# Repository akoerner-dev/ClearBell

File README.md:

# ClearBell — Smart-Doorbell (ESP32-S3, Hardware + Firmware)

🇬🇧 [English version](README.en.md)

Selbst entwickeltes Türklingelsystem für ein Zweifamilienhaus — vollständig
eigenentwickelt von der Schaltung über das PCB-Layout bis zur Firmware.
Das Projekt dokumentiert nicht nur *was* gebaut wurde, sondern die
**begründeten Technikentscheidungen** dahinter.

> Leitsatz des Projekts: **„Keep it simple, but working."**

**Aktuelle Generation: V0.2** — Redesign auf den ESP32-S3. Beide Platinen sind fertig
verlegt, bei PCBWay gefertigt und bestückt und in Betrieb genommen. Die erste Generation läuft
im Haus und liegt im [Archiv](archiv/V0.1/).

| Außeneinheit V0.2 | Inneneinheit V0.2 |
|---|---|
|  |  |
| 110 × 60 mm, 4 Lagen, 12 V DC | 98 × 60 mm, 4 Lagen, USB-C |

---

## Überblick

Eine **Außeneinheit** an der Haustür und zwei baugleiche **Inneneinheiten**
(je eine pro Wohnung). Klingeln und Türöffnen laufen als quittierte,
gegen Replay abgesicherte Transaktionen über WLAN/UDP.

| Merkmal | V0.2 |
|---|---|
| Controller | ESP32-S3-WROOM-1-N16R8 (16 MB Flash, 8 MB PSRAM), beide Einheiten |
| Stromversorgung außen | 12 V DC (SELV) → 3,3 V mit LMR33630; Polyfuse, TVS-Diode, Verpolschutz |
| Stromversorgung innen | USB-C 5 V → 3,3 V mit TLV62568 |
| Programmierung | natives USB (USB-Serial-JTAG) — innen über die USB-C-Buchse, außen über eine zusätzliche Service-USB-C |
| Bedienung | kapazitive Touch-Taster mit Bronze-Elektroden, ESD-geschützt |
| Audio | MAX98357A I2S-Class-D, Visaton K 50 FL (außen) / K 50 SQ (innen) |
| Mikrofon | Infineon IM72D128V01 (PDM, IP57) auf beiden Einheiten |
| Anzeige | zweifarbige Status-LED (grün / rot, zusammen bernstein) |
| Türöffner | Low-Side-MOSFET mit Freilaufdiode |
| Kommunikation | WLAN + UDP über den Heim-Router, Türbefehl per HMAC-SHA256 authentifiziert |

---

## Was sich gegenüber V0.1 geändert hat — und warum

- **ESP32-S3 statt ESP32.** Natives USB: Flashen und Logs ohne UART-Adapter und ohne
  Tastendruck. PSRAM für Audiopuffer, Flash-Reserve für zwei OTA-Partitionen, vom
  Hersteller zugesagte Verfügbarkeit bis 2033.
- **Mikrofon auf beiden Einheiten** — als Vorbereitung für späteres Wechselsprechen.
  Die Wahl fiel auf ein PDM-Mikrofon, das direkt an 3,3 V läuft: kein zweiter
  Spannungsbereich, keine Pegelwandler.
- **Keine SD-Karte mehr.** Die Klingeltöne sollen im Flash liegen und über die
  Statusseite getauscht werden — ein Steckverbinder und ein mechanischer Fehlerpfad weniger.
- **4 Lagen statt 2.** Beide Innenlagen sind Masse; jede Signallage hat ihre Bezugsfläche direkt
  darunter. Grund: Bei 1,6 mm liegt der dicke Kern zwangsläufig zwischen den Innenlagen, eine
  eigene Versorgungslage brächte dort kaum Flächenkapazität. Bekannte Abweichung (Inneneinheit):
  Eine 3,3-V-Leitung verläuft auf In2 und unterbricht dort die Massefläche.
  USB D+/D−, I2S_BCLK, I2S_WS und LED_RED auf der Unterseite kreuzen diesen Schlitz; ihr Rückstrom
  muss ausweichen. Funktional unkritisch bei USB Full Speed, aus EMV-Sicht aber vermeidbar.
  Behebung in V0.3: Leitung auf eine Außenlage verlegen, In2 wieder geschlossen.
- **Vias neben den Pads, nicht darin.** Ein Via im Pad zieht beim Reflow Lot ab. Der DRC
  prüft das nicht — deshalb eigene Prüfskripte über alle Vias und Pads.
- **Touch ohne Shield/Guard.** Die Bronze-Elektroden bleiben frei zugänglich. Gegen Drift
  durch Feuchte ist eine adaptive Baseline in der Firmware vorgesehen; die ESD-Dioden haben
  nur 0,5 pF, damit die Empfindlichkeit erhalten bleibt.
- **Türöffner-Freilaufdiode auf 1 A ausgelegt** (SMA-Gehäuse). In V0.1 saß dort eine
  Signaldiode, die für den Spulenstrom des Türöffners zu klein war.

Der Funk-Transport bleibt WLAN/UDP über den Router — ESP-NOW wurde an den echten
Montageorten gemessen und verworfen, siehe
[`docs/Funkvalidierung_ESPNOW.md`](docs/Funkvalidierung_ESPNOW.md).

---

## Repo-Struktur

```
clearbell/
├── hardware/                  V0.2, KiCad 10
│   ├── Ausseneinheit/         Schaltplan, Platine, Schaltplan.pdf
│   │   └── fertigung/         Gerber-ZIP, Stückliste, Bestückungsdaten
│   └── Inneneinheit/          dito
├── firmware/                  V0.2-Firmware (ESP-IDF), Werkzeuge, Testprotokoll
├── docs/
│   ├── img/                   3D-Ansichten V0.2
│   ├── pcbway-review/         Bewertung der PCBWay-Platinen mit Fotos (DE/EN)
│   ├── Softwarearchitektur_V0.2.md      Firmware-Architektur, Laufzeit, Sicherheit
│   ├── Softwarearchitektur_V0.2.en.md   dasselbe auf Englisch
│   └── Funkvalidierung_ESPNOW.md
└── archiv/V0.1/               erste Generation: Hardware, Firmware, Dashboard, Dokumentation
```

---

## Fertigung

| | |
|---|---|
| Lagenaufbau | 4 Lagen, 1,6 mm, FR-4 (S1000H, TG150), 1 oz außen und innen, keine Impedanzkontrolle |
| Oberfläche | HAL bleifrei, Lötstopplack grün, Bestückungsdruck weiß (nur oben) |
| Bestückung | einseitig, maschinell — außen 56, innen 33 Bauteile |
| Stückliste | je Einheit in `fertigung/`, mit Spalte „Ersatz zulässig" (kritische Teile ohne Ersatz) |
| Prüfung | DRC und ERC ohne Befund |

### Erfahrung mit PCBWay

Leiterplatten und Bestückung der V0.2 hat **[PCBWay](https://www.pcbway.com)** übernommen. Die Leiterplatten
wurden im Rahmen eines Sponsorings gefertigt, Bestückung und Bauteile habe ich selbst bezahlt.

Mein Fazit als Leiterplattenentwickler, der beruflich fast täglich Platinen in der Hand hat:

- **Leiterplatten sehr gut:** Lötstopp und Bestückungsdruck sauber und passgenau, HAL-Oberfläche gleichmäßig, keine Delamination,
  Platinen plan und gratfrei.
- **Bestückung sehr gut:** alle Bauteile lagerichtig, kritische Stellen (USB-C, QFN-Audioverstärker, ESP32-S3-Modul)
  ohne Brücken verlötet.
- **Auf Anhieb funktionsfähig:** Inbetriebnahme und 24-Stunden-Dauertest ohne einen einzigen Fertigungsfehler.
- **Kommunikation sehr gut:** fachlich sinnvolle Rückfragen zur Stückliste, Auftragsfortschritt auf der Website
  Schritt für Schritt nachvollziehbar.

Ich würde PCBWay wieder beauftragen.

📋 [**Ausführliche Bewertung mit Fotos**](docs/pcbway-review/README.md) · 🇬🇧 [English version](docs/pcbway-review/README.en.md)

---

## Firmware

Die **V0.2-Firmware** liegt unter [`firmware/`](firmware/README.md): ein ESP-IDF-Projekt (v5.5.5) mit dem
Arduino-Core als Komponente, ein Image für außen und eins für innen. Sie ist portiert, auf allen drei Boards
getestet und am 12.11.2026 abgenommen. Enthalten sind unter anderem ein authentifiziertes Protokoll mit Sitzungen,
Türbefehl per Challenge–Response, Touch mit adaptiver Baseline, Statusseite mit Gerätepasswort, Fern-Öffnen per
Push aufs Handy, Einrichtung ohne PC über ein eigenes WLAN und signierte Updates mit Rückfall. Den Stand jedes
Schritts und die Belege zeigen das [Firmware-README](firmware/README.md) und das
[Testprotokoll](firmware/docs/Testprotokoll.md). Offen sind noch der 72-h-Dauertest und einige Handprüfungen.

Die Firmware der ersten Generation (Arduino, quittiertes UDP-Protokoll, HMAC-gesicherter Türbefehl, eigener
WAV-Player) läuft weiter im Haus und liegt unter [`archiv/V0.1/firmware/`](archiv/V0.1/firmware/).

**Wie die V0.2-Firmware aufgebaut ist und warum, beschreibt ein eigenes Dokument:** Architektur und
Ausführungsmodell, authentifiziertes Protokoll, Startsequenz und Laufzeitverhalten,
Datenhaltung und Flash-Aufteilung, ein Sicherheitskapitel mit Angreifermodell,
**offen benannten Restrisiken** und einem Abgleich mit ETSI EN 303 645, Fehlerverhalten,
Portierungsplan und Teststrategie. Die aktuelle Revision 2 ist das Ergebnis eines
kritischen Reviews der ersten Fassung mit 29 Befunden.

📄 [**Softwarearchitektur V0.2**](docs/Softwarearchitektur_V0.2.md) · 🇬🇧 [English version](docs/Softwarearchitektur_V0.2.en.md)

Was dort bereits läuft und was noch Entwurf ist, ist durchgehend gekennzeichnet — ebenso die
fünf Verhaltensfragen, die bewusst noch offen sind.

---

## Stand

- **V0.2:** Platinen am 24.10.2026 von PCBWay geliefert, Leiterplatten und Bestückung ohne Mangel
  ([Bewertung](docs/pcbway-review/README.md)). Inbetriebnahme beider Einheiten bestanden (Versorgung, USB/Flash,
  Audio, Mikrofon, Touch, Türausgang, WLAN). Die neue [Firmware](firmware/README.md) ist portiert und am
  12.11.2026 abgenommen; alle drei Boards (eine Außen-, zwei Inneneinheiten) liefen 24 Stunden ohne Neustart
  und ohne fehlgeschlagenes Klingeln. Derzeit läuft die Härtung (verschlüsselter Schlüsselspeicher, Sicherheitstests).
  Noch offen: Test mit dem echten Türöffner und Funktest am Montageort, sobald die Gehäuse gebaut sind.
- **V0.1:** läuft im Haus; WLAN/UDP-Transport im Dauertest ohne Paketverlust.

---

## Hinweise

- **Datenblätter** der verwendeten Bauteile sind aus Urheberrechtsgründen **nicht** enthalten —
  sie sind über die Herstellerseiten frei verfügbar; die Typen stehen in den Stücklisten.
- Die eigene KiCad-Bibliothek ist in Schaltplan und Platine eingebettet. Die meisten
  **3D-Modelle** stammen aus der KiCad-Standardbibliothek und erscheinen in jeder
  KiCad-10-Installation; zehn Bauteile nutzen Herstellermodelle (Littelfuse, Panasonic,
  Infineon, TI, WAGO), die aus Lizenzgründen nicht enthalten sind — dort zeigt die
  3D-Ansicht nur die Pads.
- Netzwerknamen, Passwörter und kryptografische Schlüssel sind nicht im Repo.
- **Sicherheitslücken** bitte vertraulich melden, nicht als Issue — wie, steht in
  [`SECURITY.md`](SECURITY.md).

## Lizenz

[MIT](LICENSE) © 2026 André Körner

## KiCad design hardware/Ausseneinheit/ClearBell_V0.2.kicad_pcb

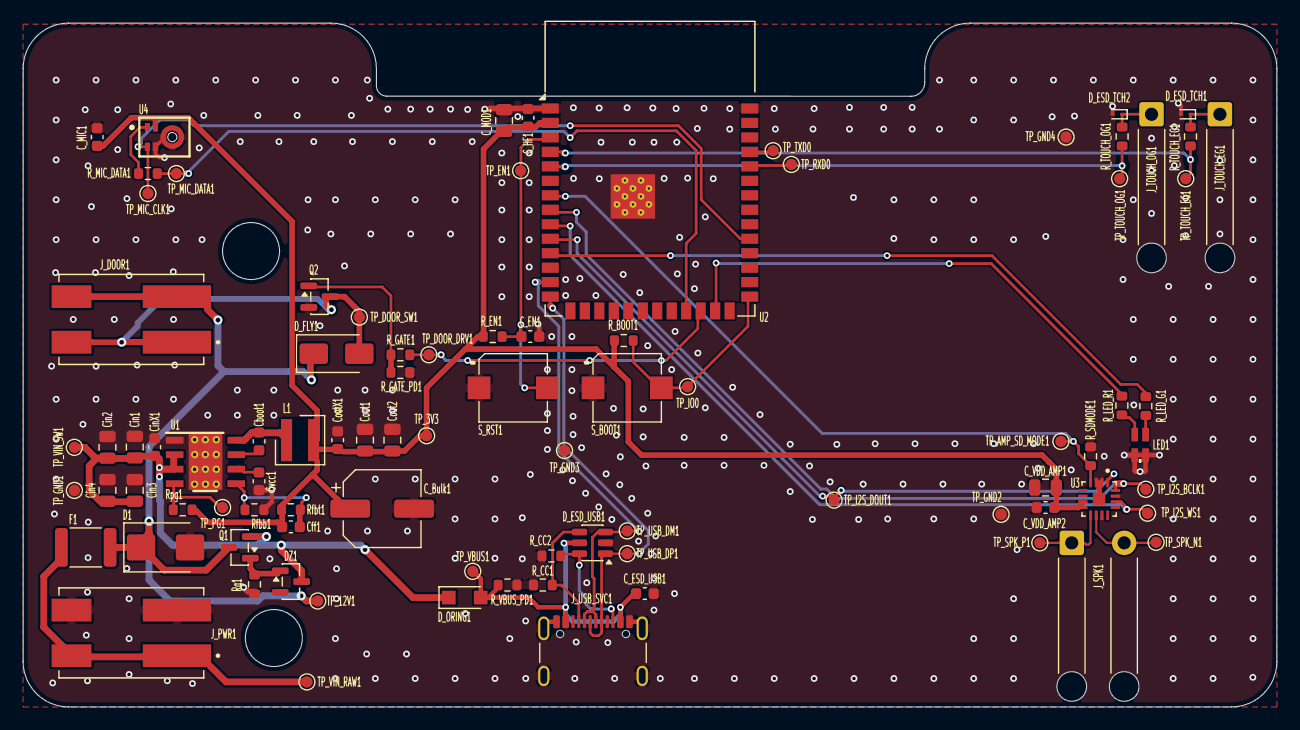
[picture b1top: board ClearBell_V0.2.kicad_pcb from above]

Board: 4 copper layers, 110.0 x 60.0 mm, 88 parts (0 on the bottom side), 40 nets.

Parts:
C_Bulk1: 100u; CP_Elec_6.3x5.4
C_EN1: 1u; C_0603_1608Metric
C_ESD_USB1: 100n; C_0603_1608Metric
C_HF1: 100n; C_0603_1608Metric
C_MIC1: 100n; C_0603_1608Metric
C_MOD1: 22u; C_0805_2012Metric
C_VDD_AMP1: 10u; C_0805_2012Metric
C_VDD_AMP2: 100n; C_0603_1608Metric
Cboot1: 100n; C_0603_1608Metric
Cff1: DNP; C_0603_1608Metric
Cin1, Cin2, Cin3, Cin4: 10u; C_0805_2012Metric
CinX1: 220n; C_0603_1608Metric
Cout1, Cout2: 22u; C_0805_2012Metric
CoutX1: 100n; C_0603_1608Metric
Cvcc1: 1u; C_0603_1608Metric
D1: SMBJ15A; D_SMB
DZ1: BZX84-C6V2; SOT-23
D_ESD_TCH1, D_ESD_TCH2: ESD9L5.0ST5G; D_SOD-923
D_ESD_USB1: USBLC6-4SC6; SOT-23-6
D_FLY1: S1A; D_SMA
D_ORING1: PMEG3010ER; Nexperia_CFP3_SOD-123W
F1: 1812L150/24MR; Fuse_1812_4532Metric
J_DOOR1: 2060-452/998-404; WAGO_2060-452_998-404
J_PWR1: 2060-452/998-404; WAGO_2060-452_998-404
J_SPK1: Loetpads Lautsprecher; SolderWire-0.5sqmm_1x02_P4.6mm_D0.9mm_OD2.1mm_Relief
J_TOUCH_EG1: Loetpad Elektrode EG; SolderWire-0.5sqmm_1x01_D0.9mm_OD2.1mm_Relief
J_TOUCH_OG1: Loetpad Elektrode OG; SolderWire-0.5sqmm_1x01_D0.9mm_OD2.1mm_Relief
J_USB_SVC1: USB4105-GF-A-120; USB_C_Receptacle_GCT_USB4105-xx-A_16P_TopMnt_Horizontal
L1: 1.8u; L_Wurth_WE-MAPI-4020HT
LED1: APHBM2012LSURKCGKC; LED_Kingbright_APHBM2012_2x1.25mm
Q1: PJA3415AE-AU; SOT-23
Q2: IRLML6344TRPBF; SOT-23
R_BOOT1: 10k; R_0603_1608Metric
R_CC1, R_CC2: 5k1; R_0603_1608Metric
R_EN1: 10k; R_0603_1608Metric
R_GATE1: 100; R_0603_1608Metric
R_GATE_PD1: 100k; R_0603_1608Metric
R_LED_G1: 750R; R_0603_1608Metric
R_LED_R1: 750R; R_0603_1608Metric
R_MIC_DATA1: 100; R_0603_1608Metric
R_SDMODE1: 100k; R_0603_1608Metric
R_TOUCH_EG1: 1k; R_0603_1608Metric
R_TOUCH_OG1: 1k; R_0603_1608Metric
R_VBUS_PD1: 1k; R_0603_1608Metric
Rfbb1: 43k2; R_0603_1608Metric
Rfbt1: 100k; R_0603_1608Metric
Rg1: 100k; R_0603_1608Metric
Rpg1: 100k; R_0603_1608Metric
S_BOOT1: EVP-BD6C1A000
S_RST1: EVP-BD6C1A000
TP_3V3, TP_12V1: TestPoint_Pad_D1.0mm
TP_AMP_SD_MODE1: TestPoint_Pad_D1.0mm
TP_DOOR_DRV1: TestPoint_Pad_D1.0mm
TP_DOOR_SW1: TestPoint_Pad_D1.0mm
TP_EN1: TestPoint_Pad_D1.0mm
TP_GND1, TP_GND2, TP_GND3, TP_GND4: TestPoint_Pad_D1.0mm
TP_I2S_BCLK1, TP_I2S_DOUT1, TP_I2S_WS1: TestPoint_Pad_D1.0mm
TP_IO0: TestPoint_Pad_D1.0mm
TP_MIC_CLK1: TestPoint_Pad_D1.0mm
TP_MIC_DATA1: TestPoint_Pad_D1.0mm
TP_PG1: TestPoint_Pad_D1.0mm
TP_RXD0: TestPoint_Pad_D1.0mm
TP_SPK_N1: TestPoint_Pad_D1.0mm
TP_SPK_P1: TestPoint_Pad_D1.0mm
TP_TOUCH_EG1: TestPoint_Pad_D1.0mm
TP_TOUCH_OG1: TestPoint_Pad_D1.0mm
TP_TXD0: TestPoint_Pad_D1.0mm
TP_USB_DM1: TestPoint_Pad_D1.0mm
TP_USB_DP1: TestPoint_Pad_D1.0mm
TP_VBUS1: TestPoint_Pad_D1.0mm
TP_VIN_RAW1: TestPoint_Pad_D1.0mm
TP_VIN_SW1: TestPoint_Pad_D1.0mm
U1: LMR33630CDDAR; DDA0008J
U2: ESP32-S3-WROOM-1-N16R8; ESP32-S3-WROOM-1
U3: MAX98357AETE+T; QFN50P300X300X80-17N
U4: IM72D128V01; IFX-PG-LLGA-5-4

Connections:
+3V3: C_Bulk1.1, C_HF1.1, C_MIC1.1, C_MOD1.1, C_VDD_AMP1.1, C_VDD_AMP2.1, Cff1.1, Cout1.1, Cout2.1, CoutX1.1, L1.2, R_BOOT1.1, R_EN1.1, Rfbt1.1, Rpg1.2, TP_3V3.1 (1_1), U2.2 (3V3), U3.7 (VDD), U3.8 (VDD), U4.2 (VDD)
+12V: D1.1 (K), D_FLY1.1 (K), F1.2, J_DOOR1.2_1 (2), J_DOOR1.2_2 (2), Q1.3 (D), TP_12V1.1 (1_1)
/BOOT: Cboot1.1, U1.7 (BOOT)
/DOOR_GATE: Q2.1 (G), R_GATE1.2, R_GATE_PD1.1
/DOOR_SW: D_FLY1.2 (A), J_DOOR1.1_1 (1), J_DOOR1.1_2 (1), Q2.3 (D), TP_DOOR_SW1.1 (1_1)
/EN: C_EN1.1, R_EN1.2, S_RST1.2, TP_EN1.1 (1_1), U2.3 (EN)
/FB: Cff1.2, Rfbb1.1, Rfbt1.2, U1.5 (FB)
/GATE_Q1: DZ1.1 (A), Q1.1 (G), Rg1.1
/IO0: R_BOOT1.2, S_BOOT1.2, TP_IO0.1 (1_1), U2.27 (IO0)
/PG: Rpg1.1, TP_PG1.1 (1_1), U1.4 (PG)
/SPK_N: J_SPK1.2, TP_SPK_N1.1 (1_1), U3.10 (OUTN)
/SPK_P: J_SPK1.1, TP_SPK_P1.1 (1_1), U3.9 (OUTP)
/SW: Cboot1.2, L1.1, U1.8 (SW)
/TCH_EG_ELEC: D_ESD_TCH1.1 (K), J_TOUCH_EG1.1 (Pin_1_1), R_TOUCH_EG1.1
/TCH_OG_ELEC: D_ESD_TCH2.1 (K), J_TOUCH_OG1.1 (Pin_1_1), R_TOUCH_OG1.1
/VBUS: C_ESD_USB1.1, D_ESD_USB1.5 (VBUS), D_ORING1.2 (A), J_USB_SVC1.A4 (VBUS), J_USB_SVC1.A9 (VBUS), J_USB_SVC1.B4 (VBUS), J_USB_SVC1.B9 (VBUS), R_VBUS_PD1.1, TP_VBUS1.1 (1_1)
/VCC_U1: Cvcc1.1, U1.6 (VCC)
/VIN_RAW: F1.1, J_PWR1.1_1 (1), J_PWR1.1_2 (1), TP_VIN_RAW1.1 (1_1)
AMP_SD_MODE: R_SDMODE1.1, TP_AMP_SD_MODE1.1 (1_1), U2.7 (IO7), U3.4 (~SD_MODE)
CC1: D_ESD_USB1.4 (I/O3), J_USB_SVC1.A5 (CC1), R_CC1.1
CC2: D_ESD_USB1.6 (I/O4), J_USB_SVC1.B5 (CC2), R_CC2.1
DOOR_DRV: R_GATE1.1, TP_DOOR_DRV1.1 (1_1), U2.24 (IO47)
GND: C_Bulk1.2, C_EN1.2, C_ESD_USB1.2, C_HF1.2, C_MIC1.2, C_MOD1.2, C_VDD_AMP1.2, C_VDD_AMP2.2, Cin1.2, Cin2.2, Cin3.2, Cin4.2, CinX1.2, Cout1.2, Cout2.2, CoutX1.2, Cvcc1.2, D1.2 (A), D_ESD_TCH1.2 (A), D_ESD_TCH2.2 (A), D_ESD_USB1.2 (GND), J_PWR1.2_1 (2), J_PWR1.2_2 (2), J_USB_SVC1.A1 (GND), J_USB_SVC1.A12 (GND), J_USB_SVC1.B1 (GND), J_USB_SVC1.B12 (GND), J_USB_SVC1.SH (SHIELD), LED1.2 (K1), LED1.3 (K2), Q2.2 (S), R_CC1.2, R_CC2.2, R_GATE_PD1.2, R_SDMODE1.2, R_VBUS_PD1.2, Rfbb1.2, Rg1.2, S_BOOT1.1, S_RST1.1, TP_GND1.1 (1_1), TP_GND2.1 (1_1), TP_GND3.1 (1_1), TP_GND4.1 (1_1), U1.1 (PGND), U1.9 (AGND), U2.1 (GND), U2.40 (GND), U2.41 (GND), U3.2 (GAIN_SLOT), U3.3 (GND), U3.11 (GND), U3.15 (GND), U3.17 (PAD), U4.4 (SELECT), U4.5 (GND)
I2S_BCLK: TP_I2S_BCLK1.1 (1_1), U2.8 (IO15), U3.16 (BCLK)
I2S_DOUT: TP_I2S_DOUT1.1 (1_1), U2.10 (IO17), U3.1 (DIN)
I2S_WS: TP_I2S_WS1.1 (1_1), U2.9 (IO16), U3.14 (LRCLK)
LED_GRN: R_LED_G1.2, U2.11 (IO18)
LED_RED: R_LED_R1.2, U2.25 (IO48)
MIC_CLK: TP_MIC_CLK1.1 (1_1), U2.31 (IO38), U4.3 (CLOCK)
MIC_DATA: R_MIC_DATA1.1, TP_MIC_DATA1.1 (1_1), U2.23 (IO21)
unnamed: LED1.1 (A1), R_LED_R1.1
unnamed: LED1.4 (A2), R_LED_G1.1
unnamed: R_MIC_DATA1.2, U4.1 (DATA)
RXD0: TP_RXD0.1 (1_1), U2.36 (RXD0)
TOUCH_EG: R_TOUCH_EG1.2, TP_TOUCH_EG1.1 (1_1), U2.4 (IO4)
TOUCH_OG: R_TOUCH_OG1.2, TP_TOUCH_OG1.1 (1_1), U2.5 (IO5)
TXD0: TP_TXD0.1 (1_1), U2.37 (TXD0)
USB_DM: D_ESD_USB1.3 (I/O2), J_USB_SVC1.A7 (D-), J_USB_SVC1.B7 (D-), TP_USB_DM1.1 (1_1), U2.13 (USB_D-)
USB_DP: D_ESD_USB1.1 (I/O1), J_USB_SVC1.A6 (D+), J_USB_SVC1.B6 (D+), TP_USB_DP1.1 (1_1), U2.14 (USB_D+)
VIN_SW: Cin1.1, Cin2.1, Cin3.1, Cin4.1, CinX1.1, DZ1.3 (K), D_ORING1.1 (K), Q1.2 (S), TP_VIN_SW1.1 (1_1), U1.2 (VIN), U1.3 (EN)

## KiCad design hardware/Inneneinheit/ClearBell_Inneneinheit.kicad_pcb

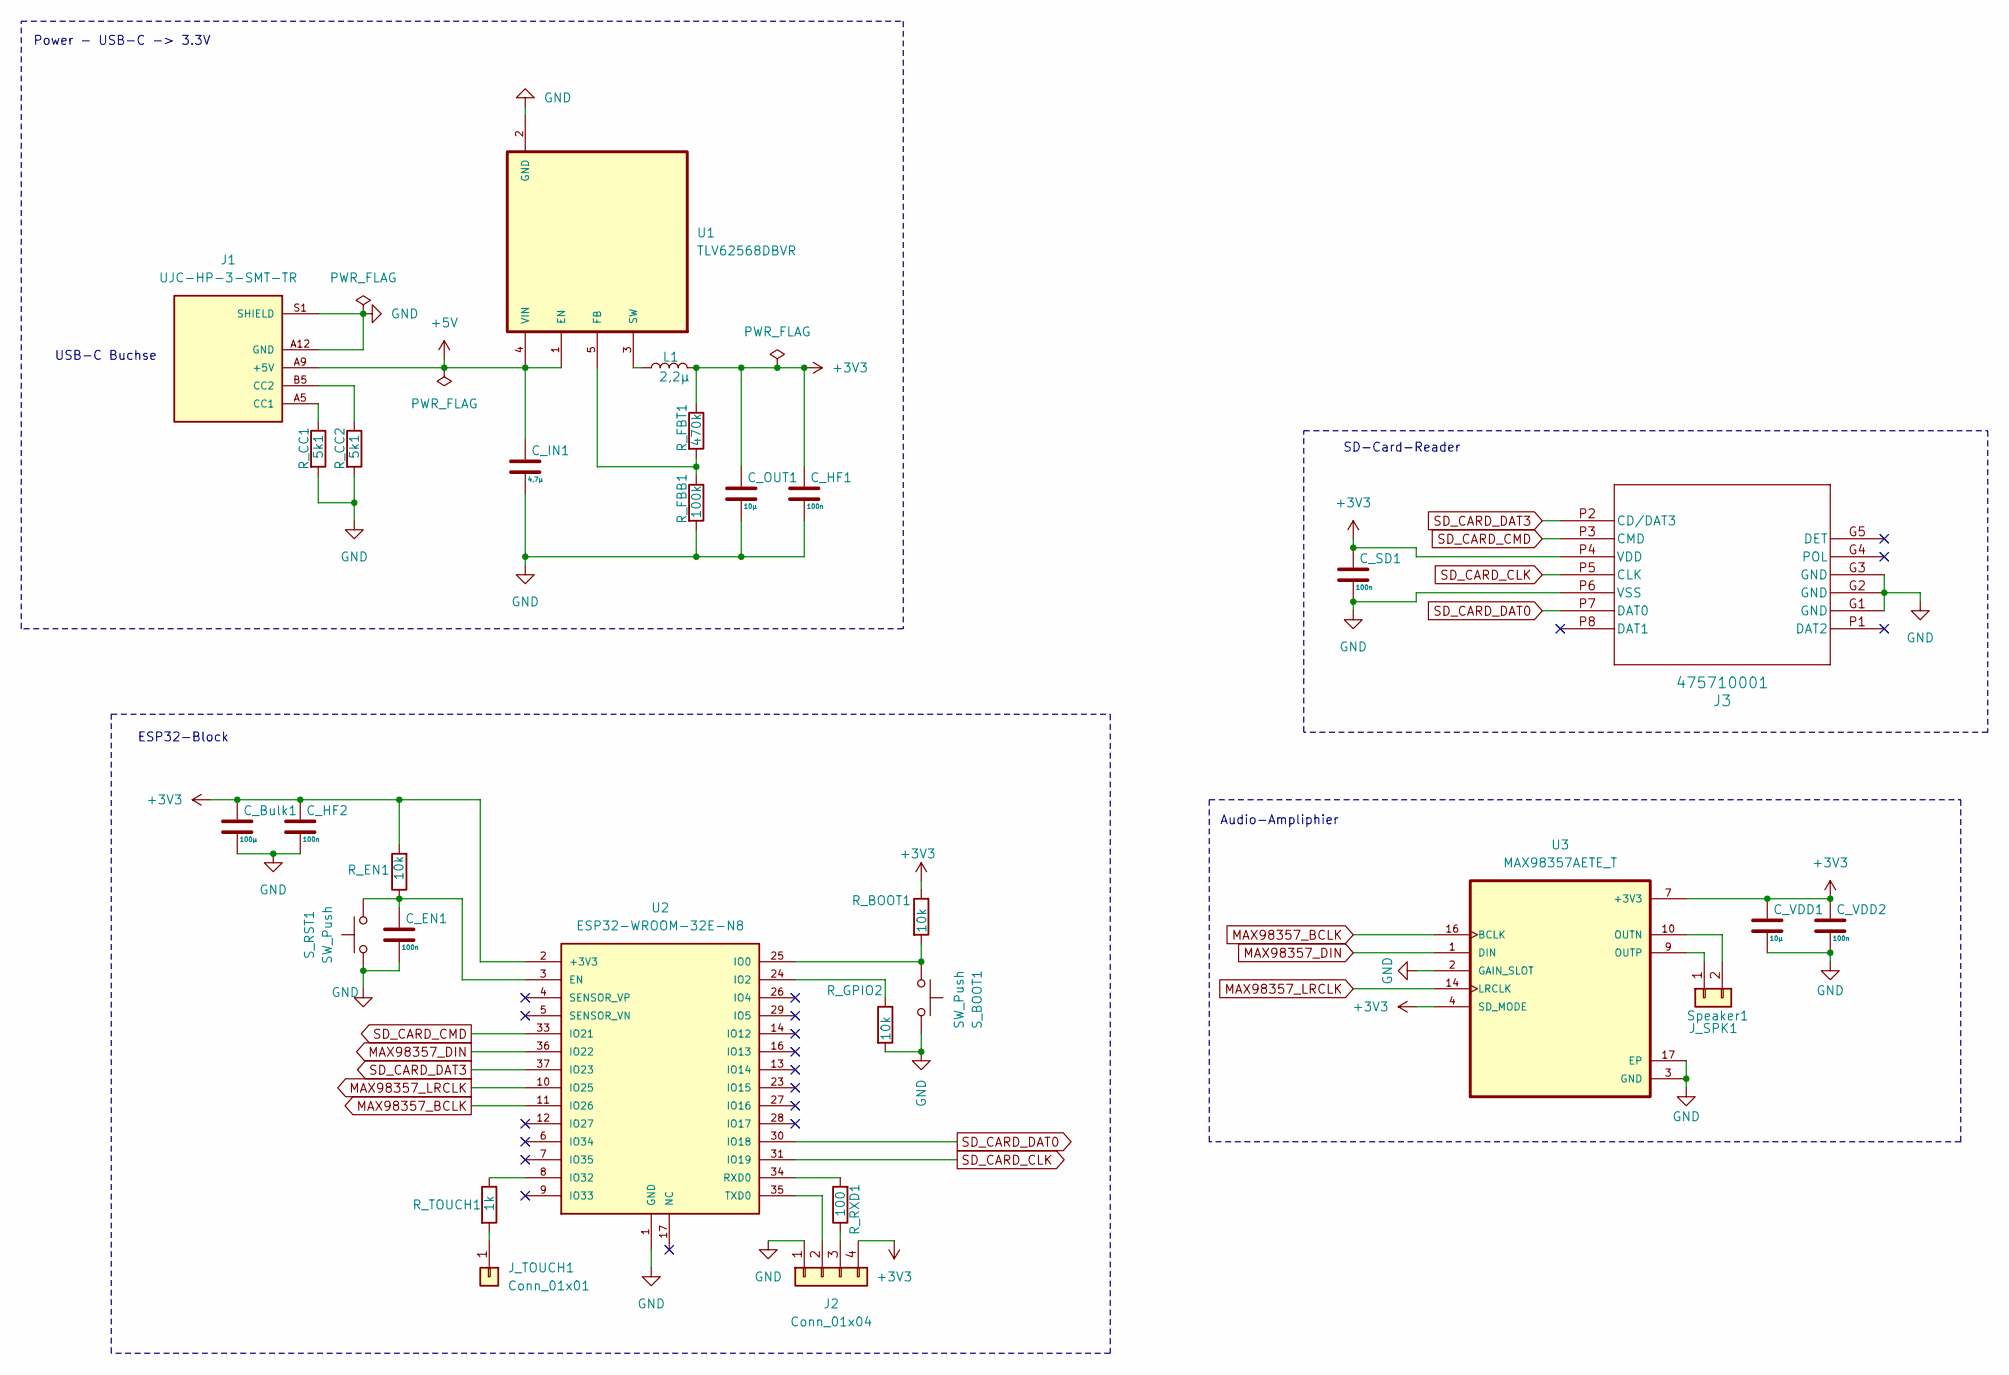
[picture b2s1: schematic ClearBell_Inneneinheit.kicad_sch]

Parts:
C_Bulk1: 100µ; C_Elec_6.3x5.4
C_EN1: 100n; C_0603_1608Metric_Pad1.08x0.95mm_HandSolder
C_HF1, C_HF2: 100n; C_0603_1608Metric_Pad1.08x0.95mm_HandSolder
C_IN1: 4,7µ; C_0603_1608Metric_Pad1.08x0.95mm_HandSolder
C_OUT1: 10µ; C_0603_1608Metric_Pad1.08x0.95mm_HandSolder
C_SD1: 100n; C_0603_1608Metric_Pad1.08x0.95mm_HandSolder
C_VDD1: 10µ; C_0603_1608Metric_Pad1.08x0.95mm_HandSolder
C_VDD2: 100n; C_0603_1608Metric_Pad1.08x0.95mm_HandSolder
J1: UJC-HP-3-SMT-TR; CUI_UJC-HP-3-SMT-TR; PARTREV 04/30/2020
J2: Conn_01x04; PinSocket_1x04_P2.54mm_Horizontal
J3: 475710001; MOLEX MICRO SD CARD_475710001; MANUFACTURER_PART_NUMBER 0475710001; Digi-Key_Part_Number WM9731CT-ND
J_SPK1: Speaker1; Wago_2086-1202
J_TOUCH1: Conn_01x01; TestPoint_Pad_2.0x2.0mm
L1: 2,2µ; L_Wurth_WE-MAPI-4020HT; MANUFACTURER_PART_NUMBER SDER041H-2R2MS; Digi-Key_Part_Number 2037-SDER041H-2R2MSCT-ND
R_BOOT1: 10k; R_0603_1608Metric_Pad0.98x0.95mm_HandSolder
R_CC1, R_CC2: 5k1; R_0603_1608Metric_Pad0.98x0.95mm_HandSolder
R_EN1: 10k; R_0603_1608Metric_Pad0.98x0.95mm_HandSolder
R_FBB1: 100k; R_0603_1608Metric_Pad0.98x0.95mm_HandSolder
R_FBT1: 470k; R_0603_1608Metric_Pad0.98x0.95mm_HandSolder
R_GPIO2: 10k; R_0603_1608Metric_Pad0.98x0.95mm_HandSolder
R_RXD1: 100; R_0603_1608Metric_Pad0.98x0.95mm_HandSolder
R_TOUCH1: 1k; R_0603_1608Metric_Pad0.98x0.95mm_HandSolder
S_BOOT1: SW_Push; CK_PTS526; MANUFACTURER_PART_NUMBER PTS526SK15SMTR2 LFS; Digi-Key_Part_Number CKN12221-1-ND
S_RST1: SW_Push; CK_PTS526; MANUFACTURER_PART_NUMBER PTS526SK15SMTR2 LFS; Digi-Key_Part_Number CKN12221-1-ND
U1: TLV62568DBVR; SOT95P280X145-5N; Digi-Key_Part_Number 296-47359-1-ND
U2: ESP32-WROOM-32E-N8; ESP32WROOM32EN8; MOUSER_PART_NUMBER 356-ESP32WRM32E164PH
U3: MAX98357AETE_T; QFN50P300X300X80-17N; MANUFACTURER_PART_NUMBER MAX98357AETE+T; Digi-Key_Part_Number MAX98357AETE+TCT-ND

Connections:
+3V3: C_Bulk1.1, C_HF1.1, C_HF2.1, C_OUT1.1, C_SD1.1, C_VDD1.1, C_VDD2.1, J2.4, J3.P4 (VDD), L1.2, R_BOOT1.1, R_EN1.2, R_FBT1.1, U2.2 (+3V3), U3.4 (SD_MODE), U3.7 (+3V3), U3.8 (+3V3)
+5V: C_IN1.1, J1.A9 (+5V), J1.B9 (+5V), U1.1 (EN), U1.4 (VIN)
GND: C_Bulk1.2, C_EN1.2, C_HF1.2, C_HF2.2, C_IN1.2, C_OUT1.2, C_SD1.2, C_VDD1.2, C_VDD2.2, J1.A12 (GND), J1.B12 (GND), J1.S1 (SHIELD), J1.S2 (SHIELD), J1.S3 (SHIELD), J1.S4 (SHIELD), J2.1, J3.G1 (GND), J3.G2 (GND), J3.G3 (GND), J3.P6 (VSS), R_CC1.2, R_CC2.2, R_FBB1.2, R_GPIO2.2, S_BOOT1.2, S_RST1.1, U1.2 (GND), U2.1 (GND), U2.15 (GND), U2.38 (GND), U2.39 (GND), U2.40 (GND), U2.41 (GND), U2.42 (GND), U2.43 (GND), U2.44 (GND), U2.45 (GND), U2.46 (GND), U2.47 (GND), U3.2 (GAIN_SLOT), U3.3 (GND), U3.11 (GND), U3.15 (GND), U3.17 (EP)
MAX98357_BCLK: U2.11 (IO26), U3.16 (BCLK)
MAX98357_DIN: U2.36 (IO22), U3.1 (DIN)
MAX98357_LRCLK: U2.10 (IO25), U3.14 (LRCLK)
unnamed: J1.A5 (CC1), R_CC1.1
unnamed: J1.B5 (CC2), R_CC2.1
unnamed: J2.2, U2.35 (TXD0)
unnamed: J2.3, R_RXD1.1
unnamed: J_SPK1.1, U3.9 (OUTP)
unnamed: J_SPK1.2, U3.10 (OUTN)
unnamed: J_TOUCH1.1 (Pin_1_1), R_TOUCH1.2
unnamed: R_FBB1.1, R_FBT1.2, U1.5 (FB)
unnamed: L1.1, U1.3 (SW)
unnamed: C_EN1.1, R_EN1.1, S_RST1.2, U2.3 (EN)
unnamed: R_BOOT1.2, S_BOOT1.1, U2.25 (IO0)
unnamed: R_GPIO2.1, U2.24 (IO2)
unnamed: R_TOUCH1.1, U2.8 (IO32)
unnamed: R_RXD1.2, U2.34 (RXD0)
SD_CARD_CLK: J3.P5 (CLK), U2.31 (IO19)
SD_CARD_CMD: J3.P3 (CMD), U2.33 (IO21)
SD_CARD_DAT0: J3.P7 (DAT0), U2.30 (IO18)
SD_CARD_DAT3: J3.P2 (CD/DAT3), U2.37 (IO23)

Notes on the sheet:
USB-C Buchse
ESP32-Block
Audio-Ampliphier
SD-Card-Reader
Power - USB-C -> 3.3V

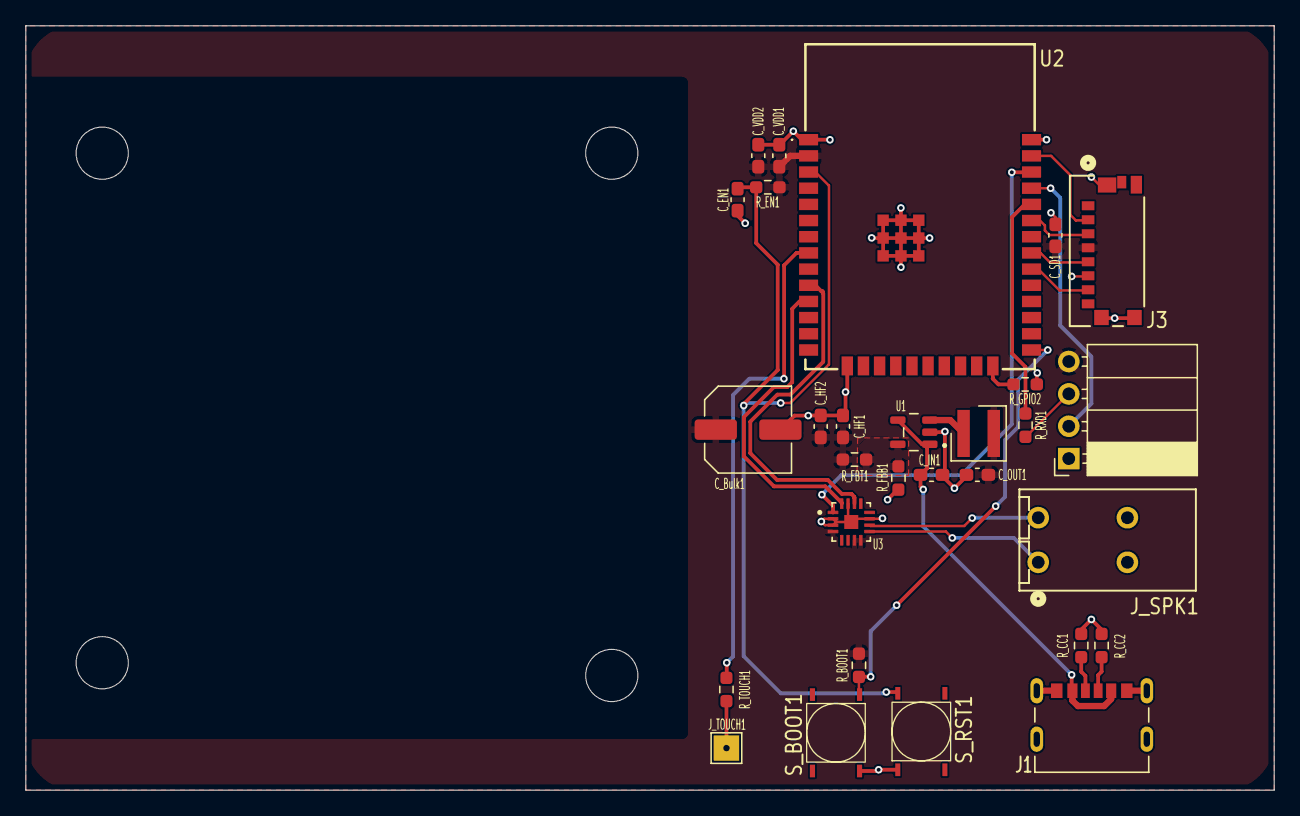
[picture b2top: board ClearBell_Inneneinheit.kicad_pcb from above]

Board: 2 copper layers, 98.0 x 60.0 mm, 30 parts (0 on the bottom side), 24 nets.

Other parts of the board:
LS1: Visatone K50 SQ

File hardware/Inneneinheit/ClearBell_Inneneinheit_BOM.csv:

"Reference","Qty","Value","DNP","Exclude from BOM","Exclude from Board","Footprint","Datasheet","Beschreibung"
"C_Bulk1","1","100µ","","","","Capacitor_SMD:C_Elec_6.3x5.4","","Unpolarized capacitor"
"C_EN1,C_HF1,C_HF2,C_SD1,C_VDD2","5","100n","","","","Capacitor_SMD:C_0603_1608Metric_Pad1.08x0.95mm_HandSolder","","Unpolarized capacitor"
"C_IN1","1","4,7µ","","","","Capacitor_SMD:C_0603_1608Metric_Pad1.08x0.95mm_HandSolder","","Unpolarized capacitor"
"C_OUT1,C_VDD1","2","10µ","","","","Capacitor_SMD:C_0603_1608Metric_Pad1.08x0.95mm_HandSolder","","Unpolarized capacitor"
"J1","1","UJC-HP-3-SMT-TR","","","","UJC-HP-3-SMT-TR:CUI_UJC-HP-3-SMT-TR","","Type C, 20 Vdc, 3 A, Right Angle, Surface Mount, Black Insulator, Power-Only USB Receptacle"
"J2","1","Conn_01x04","","","","Connector_PinSocket_2.54mm:PinSocket_1x04_P2.54mm_Horizontal","","Generic connector, single row, 01x04, script generated (kicad-library-utils/schlib/autogen/connector/)"
"J3","1","475710001","","","","MOLEX MICRO SD CARD_475710001:MOLEX MICRO SD CARD_475710001","https://www.molex.com/en-us/products/part-detail-pdf/4757100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","microSD memory card connector, push-pull, 8 contacts + detect switch, 1.10mm pitch"
"J_SPK1","1","Speaker1","","","","Wago_2086-1202:Wago_2086-1202","","Generic connector, single row, 01x02, script generated (kicad-library-utils/schlib/autogen/connector/)"
"J_TOUCH1","1","Conn_01x01","","","","TestPoint:TestPoint_Pad_2.0x2.0mm","","Generic connector, single row, 01x01, script generated (kicad-library-utils/schlib/autogen/connector/)"
"L1","1","2,2µ","","","","Inductor_SMD_Wurth:L_Wurth_WE-MAPI-4020HT","${KIPRJMOD}/Datenblätter/SDER041H-000 (B3).pdf","Shielded SMD power inductor 2.2uH +/-20%, Isat 3.1A, 45mOhm, 4.0x4.0x1.8mm"
"R_BOOT1,R_EN1,R_GPIO2","3","10k","","","","Resistor_SMD:R_0603_1608Metric_Pad0.98x0.95mm_HandSolder","","Resistor"
"R_CC1,R_CC2","2","5k1","","","","Resistor_SMD:R_0603_1608Metric_Pad0.98x0.95mm_HandSolder","","Resistor"
"R_FBB1","1","100k","","","","Resistor_SMD:R_0603_1608Metric_Pad0.98x0.95mm_HandSolder","","Resistor"
"R_FBT1","1","470k","","","","Resistor_SMD:R_0603_1608Metric_Pad0.98x0.95mm_HandSolder","","Resistor"
"R_RXD1","1","100","","","","Resistor_SMD:R_0603_1608Metric_Pad0.98x0.95mm_HandSolder","","Resistor"
"R_TOUCH1","1","1k","","","","Resistor_SMD:R_0603_1608Metric_Pad0.98x0.95mm_HandSolder","","Resistor"
"S_BOOT1,S_RST1","2","SW_Push","","","","CK_PTS526:CK_PTS526","https://www.ckswitches.com/products/switches/product-details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","Tactile switch SPST-NO 0.05A 12V, 5.2x5.2mm SMD"
"U1","1","TLV62568DBVR","","","","TLV62568DBVR:SOT95P280X145-5N","kicad-embed://tlv62568.pdf","2.5V-5.5V input, 1A high efficiency step-down buck converter in SOT23 and SOT563 package"
"U2","1","ESP32-WROOM-32E-N8","","","","ESP32-WROOM-32E-N4:ESP32WROOM32EN8","https://www.espressif.com/sites/default/files/documentation/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","Bluetooth, WiFi 802.11b/g/n, Bluetooth v4.2 +EDR, Class 1, 2 and 3 Transceiver Module 2.4GHz ~ 2.5GHz PCB Trace Surface Mount"
"U3","1","MAX98357AETE_T","","","","MAX98357AETE_T:QFN50P300X300X80-17N","https://www.analog.com/media/en/technical-documentation/data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","Tiny, Low-Cost, PCM Class D Amplifier with Class AB Performance"

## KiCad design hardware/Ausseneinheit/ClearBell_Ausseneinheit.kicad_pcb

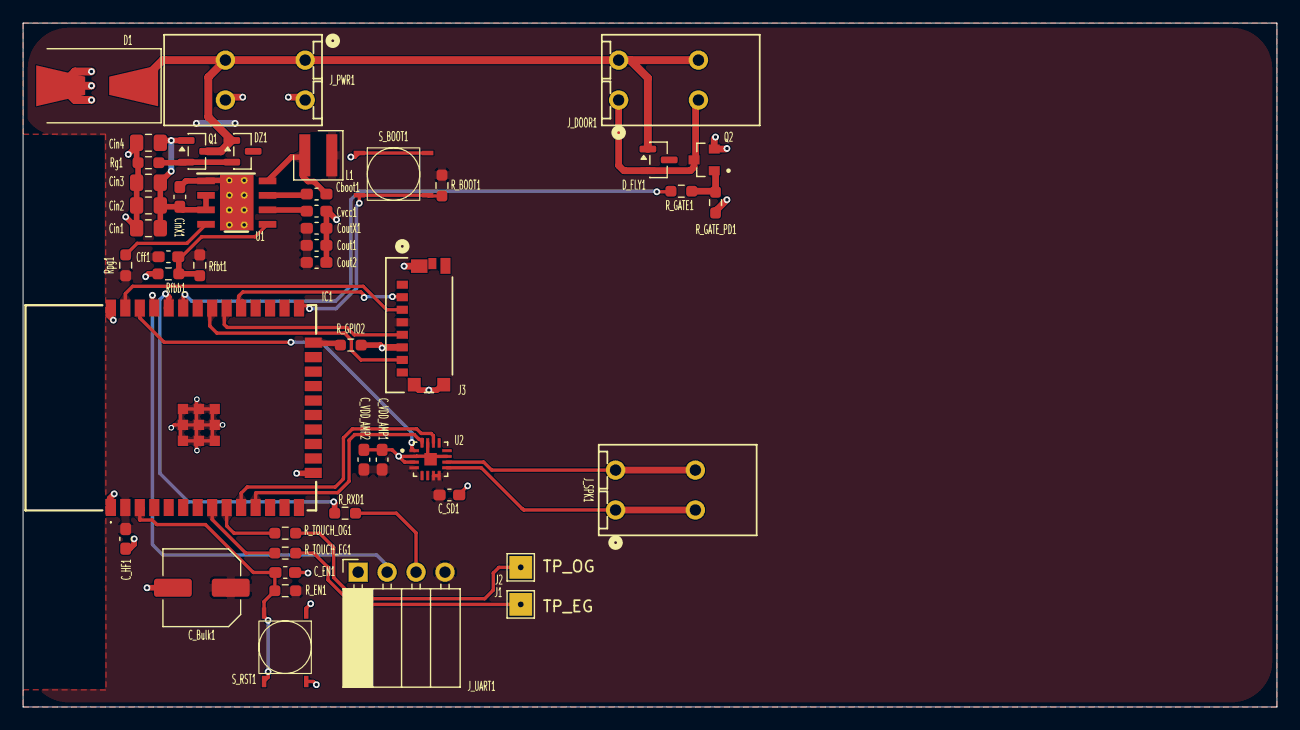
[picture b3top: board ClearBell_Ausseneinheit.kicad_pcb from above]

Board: 2 copper layers, 110.0 x 60.0 mm, 47 parts (0 on the bottom side), 32 nets.

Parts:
C_Bulk1: 100u; C_Elec_6.3x5.4
C_EN1: 100n; C_0603_1608Metric_Pad1.08x0.95mm_HandSolder
C_HF1: 100n; C_0603_1608Metric_Pad1.08x0.95mm_HandSolder
C_SD1: 100n; C_0603_1608Metric_Pad1.08x0.95mm_HandSolder
C_VDD_AMP1: 10u; C_0603_1608Metric_Pad1.08x0.95mm_HandSolder
C_VDD_AMP2: 100n; C_0603_1608Metric_Pad1.08x0.95mm_HandSolder
Cboot1: 100n; C_0603_1608Metric_Pad1.08x0.95mm_HandSolder
Cff1: DNP; C_0603_1608Metric_Pad1.08x0.95mm_HandSolder
Cin1, Cin2, Cin3, Cin4: 10u; C_0805_2012Metric_Pad1.18x1.45mm_HandSolder
CinX1: 220n; C_0603_1608Metric_Pad1.08x0.95mm_HandSolder
Cout1, Cout2: 22u; C_0603_1608Metric_Pad1.08x0.95mm_HandSolder
CoutX1: 100n; C_0603_1608Metric_Pad1.08x0.95mm_HandSolder
Cvcc1: 1u; C_0603_1608Metric_Pad1.08x0.95mm_HandSolder
D1: SMBJ15A; D_SMB-SMC_Universal_Handsoldering
DZ1: BZX84-C7V5; SOT-23
D_FLY1: 1N4148W; SOT-23
IC1: ESP32-WROOM-32E-N8; ESP32WROOM32EN8
J1: Touchpad_EG; TestPoint_Pad_2.0x2.0mm
J2: Touchpad_OG; TestPoint_Pad_2.0x2.0mm
J3: 475710001; MOLEX MICRO SD CARD_475710001
J_DOOR1: Dooropener; Wago_2086-1202
J_PWR1: WAGO_2086-1202; Wago_2086-1202
J_SPK1: Speaker1; Wago_2086-1202
J_UART1: UART; PinSocket_1x04_P2.54mm_Horizontal
L1: 4020HT_74438356018HT; L_Wurth_WE-MAPI-4020HT
Q1: DMG2305UX-7; SOT-23
Q2: IRLML6344TRPBF; TRANS_IRLML6344TRPBF
R_BOOT1: 10k; R_0603_1608Metric_Pad0.98x0.95mm_HandSolder
R_EN1: 10k; R_0603_1608Metric_Pad0.98x0.95mm_HandSolder
R_GATE1: 100; R_0603_1608Metric_Pad0.98x0.95mm_HandSolder
R_GATE_PD1: 100k; R_0603_1608Metric_Pad0.98x0.95mm_HandSolder
R_GPIO2: 10k; R_0603_1608Metric_Pad0.98x0.95mm_HandSolder
R_RXD1: 100; R_0603_1608Metric_Pad0.98x0.95mm_HandSolder
R_TOUCH_EG1: 1k; R_0603_1608Metric_Pad0.98x0.95mm_HandSolder
R_TOUCH_OG1: 1k; R_0603_1608Metric_Pad0.98x0.95mm_HandSolder
Rfbb1: 43k2; R_0603_1608Metric_Pad0.98x0.95mm_HandSolder
Rfbt1: 100k; R_0603_1608Metric_Pad0.98x0.95mm_HandSolder
Rg1: 100k; R_0603_1608Metric_Pad0.98x0.95mm_HandSolder
Rpg1: 100k; R_0603_1608Metric_Pad0.98x0.95mm_HandSolder
S_BOOT1: SW_BOOT1; CK_PTS526
S_RST1: SW_RST; CK_PTS526
U1: LMR33630ADDA; DDA0008J
U2: MAX98357AETE_T; QFN50P300X300X80-17N

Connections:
+3V3: C_Bulk1.1, C_HF1.1, C_SD1.1, C_VDD_AMP1.2, C_VDD_AMP2.2, Cff1.2, Cout1.1, Cout2.1, CoutX1.1, IC1.2 (3V3), J3.P4 (VDD), J_UART1.4, L1.2, R_BOOT1.1, R_EN1.1, Rfbt1.2, Rpg1.2, U2.4 (SD_MODE), U2.7 (+3V3), U2.8 (+3V3)
+12V: D1.1 (K), DZ1.1 (K), D_FLY1.1 (K), J_DOOR1.2, J_DOOR1.4, J_PWR1.1 (Pin_1_1), J_PWR1.3 (Pin_2_2), Q1.3 (S)
/Net-(J_SPK1-Pin_1): J_SPK1.2, J_SPK1.4, U2.10 (OUTN)
GND: C_Bulk1.2, C_EN1.2, C_HF1.2, C_SD1.2, C_VDD_AMP1.1, C_VDD_AMP2.1, Cin1.2, Cin2.2, Cin3.2, Cin4.2, CinX1.2, Cout1.2, Cout2.2, CoutX1.2, Cvcc1.2, D1.2 (A), IC1.1 (GND), IC1.15 (GND), IC1.38 (GND), IC1.39 (GND), IC1.40 (GND), IC1.41 (GND), IC1.42 (GND), IC1.43 (GND), IC1.44 (GND), IC1.45 (GND), IC1.46 (GND), IC1.47 (GND), J3.G1 (GND), J3.G2 (GND), J3.G3 (GND), J3.P6 (VSS), J_PWR1.2, J_PWR1.4, J_UART1.1, Q2.2, R_GATE_PD1.2, R_GPIO2.2, Rfbb1.2, Rg1.1, S_BOOT1.1, S_BOOT1.2, S_RST1.1, S_RST1.2, U1.1 (PGND), U1.9 (AGND), U1.V, U2.2 (GAIN_SLOT), U2.3 (GND), U2.11 (GND), U2.15 (GND), U2.17 (EP)
IRLML6344_Gate: Q2.1, R_GATE1.1, R_GATE_PD1.1
MAX98357_BCLK: IC1.11 (IO26), U2.16 (BCLK)
MAX98357_DIN: IC1.36 (IO22), U2.1 (DIN)
MAX98357_LRCLK: IC1.10 (IO25), U2.14 (LRCLK)
unnamed: DZ1.2 (A), Q1.2 (G), Rg1.2
unnamed: D_FLY1.2 (A), J_DOOR1.1 (Pin_1_1), J_DOOR1.3 (Pin_2_2), Q2.3
unnamed: C_EN1.1, IC1.3 (EN), R_EN1.2, S_RST1.3, S_RST1.4
unnamed: IC1.25 (IO0), R_BOOT1.2, S_BOOT1.3, S_BOOT1.4
unnamed: IC1.24 (IO2), R_GPIO2.1
unnamed: IC1.33 (IO21), R_GATE1.2
unnamed: IC1.8 (IO32), R_TOUCH_EG1.1
unnamed: IC1.9 (IO33), R_TOUCH_OG1.1
unnamed: IC1.34 (RXD0), R_RXD1.1
unnamed: IC1.35 (TXD0), J_UART1.2
unnamed: J1.1 (Pin_1_1), R_TOUCH_EG1.2
unnamed: J2.1 (Pin_1_1), R_TOUCH_OG1.2
unnamed: J_SPK1.1 (Pin_1_1), J_SPK1.3 (Pin_2_2), U2.9 (OUTP)
unnamed: J_UART1.3, R_RXD1.2
unnamed: Cin1.1, Cin2.1, Cin3.1, Cin4.1, CinX1.1, Q1.1 (D), U1.2 (VIN), U1.3 (EN)
unnamed: Cboot1.1, U1.7 (BOOT)
unnamed: Cff1.1, Rfbb1.1, Rfbt1.1, U1.5 (FB)
unnamed: Rpg1.1, U1.4 (PG)
unnamed: Cboot1.2, L1.1, U1.8 (SW)
unnamed: Cvcc1.1, U1.6 (VCC)
SD_Card_CLK: IC1.30 (IO18), J3.P5 (CLK)
SD_Card_CMD: IC1.37 (IO23), J3.P3 (CMD)
SD_Card_DAT0: IC1.31 (IO19), J3.P7 (DAT0)
SD_Card_DAT3/CD: IC1.29 (IO5), J3.P2 (CD/DAT3)

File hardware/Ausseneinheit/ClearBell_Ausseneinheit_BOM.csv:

"Reference","Qty","Value","DNP","Exclude from BOM","Exclude from Board","Footprint","Datasheet"
"Cboot1","1","100n","","","","Capacitor_SMD:C_0603_1608Metric_Pad1.08x0.95mm_HandSolder",""
"Cff1","1","DNP","Nicht bestücken","","","Capacitor_SMD:C_0603_1608Metric_Pad1.08x0.95mm_HandSolder",""
"Cin1,Cin2,Cin3,Cin4","4","10u","","","","Capacitor_SMD:C_0805_2012Metric_Pad1.18x1.45mm_HandSolder",""
"CinX1","1","220n","","","","Capacitor_SMD:C_0603_1608Metric_Pad1.08x0.95mm_HandSolder",""
"Cout1,Cout2","2","22u","","","","Capacitor_SMD:C_0603_1608Metric_Pad1.08x0.95mm_HandSolder",""
"CoutX1","1","100n","","","","Capacitor_SMD:C_0603_1608Metric_Pad1.08x0.95mm_HandSolder",""
"Cvcc1","1","1u","","","","Capacitor_SMD:C_0603_1608Metric_Pad1.08x0.95mm_HandSolder",""
"C_Bulk1","1","100u","","","","Capacitor_SMD:C_Elec_6.3x5.4",""
"C_EN1","1","100n","","","","Capacitor_SMD:C_0603_1608Metric_Pad1.08x0.95mm_HandSolder",""
"C_HF1","1","100n","","","","Capacitor_SMD:C_0603_1608Metric_Pad1.08x0.95mm_HandSolder",""
"C_SD1","1","100n","","","","Capacitor_SMD:C_0603_1608Metric_Pad1.08x0.95mm_HandSolder",""
"C_VDD_AMP1","1","10u","","","","Capacitor_SMD:C_0603_1608Metric_Pad1.08x0.95mm_HandSolder",""
"C_VDD_AMP2","1","100n","","","","Capacitor_SMD:C_0603_1608Metric_Pad1.08x0.95mm_HandSolder",""
"D1","1","SMBJ15A","","","","Diode_SMD:D_SMB-SMC_Universal_Handsoldering",""
"DZ1","1","BZX84-C7V5","","","","Package_TO_SOT_SMD:SOT-23",""
"D_FLY1","1","1N4148W","","","","Package_TO_SOT_SMD:SOT-23","https://www.vishay.com/docs/85748/1n4148w.pdf"
"IC1","1","ESP32-WROOM-32E-N8","","","","ESP32-WROOM-32E-N4:ESP32WROOM32EN8","https://www.espressif.com/sites/default/files/documentation/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"
"J1","1","Touchpad_EG","","","","TestPoint:TestPoint_Pad_2.0x2.0mm",""
"J2","1","Touchpad_OG","","","","TestPoint:TestPoint_Pad_2.0x2.0mm",""
"J3","1","475710001","","","","MOLEX MICRO SD CARD_475710001:MOLEX MICRO SD CARD_475710001","https://www.molex.com/en-us/products/part-detail-pdf/4757100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"
"J_DOOR1","1","Dooropener","","","","Wago_2086-1202:Wago_2086-1202",""
"J_PWR1","1","WAGO_2086-1202","","","","Wago_2086-1202:Wago_2086-1202",""
"J_SPK1","1","Speaker1","","","","Wago_2086-1202:Wago_2086-1202",""
"J_UART1","1","UART","","","","Connector_PinSocket_2.54mm:PinSocket_1x04_P2.54mm_Horizontal",""
"L1","1","4020HT_74438356018HT","","","","Inductor_SMD_Wurth:L_Wurth_WE-MAPI-4020HT","https://www.we-online.com/catalog/datasheet/74438356018HT.pdf?ki"
"Q1","1","DMG2305UX-7","","","","Package_TO_SOT_SMD:SOT-23","https://www.panjit.com.tw/upload/datasheet/PJA3415.pdf"
"Q2","1","IRLML6344TRPBF","","","","IRLML6344:TRANS_IRLML6344TRPBF",""
"Rfbb1","1","43k2","","","","Resistor_SMD:R_0603_1608Metric_Pad0.98x0.95mm_HandSolder",""
"Rfbt1","1","100k","","","","Resistor_SMD:R_0603_1608Metric_Pad0.98x0.95mm_HandSolder",""
"Rg1","1","100k","","","","Resistor_SMD:R_0603_1608Metric_Pad0.98x0.95mm_HandSolder",""
"Rpg1","1","100k","","","","Resistor_SMD:R_0603_1608Metric_Pad0.98x0.95mm_HandSolder",""
"R_BOOT1","1","10k","","","","Resistor_SMD:R_0603_1608Metric_Pad0.98x0.95mm_HandSolder",""
"R_EN1","1","10k","","","","Resistor_SMD:R_0603_1608Metric_Pad0.98x0.95mm_HandSolder",""
"R_GATE1","1","100","","","","Resistor_SMD:R_0603_1608Metric_Pad0.98x0.95mm_HandSolder",""
"R_GATE_PD1","1","100k","","","","Resistor_SMD:R_0603_1608Metric_Pad0.98x0.95mm_HandSolder",""
"R_GPIO2","1","10k","","","","Resistor_SMD:R_0603_1608Metric_Pad0.98x0.95mm_HandSolder",""
"R_RXD1","1","100","","","","Resistor_SMD:R_0603_1608Metric_Pad0.98x0.95mm_HandSolder",""
"R_TOUCH_EG1","1","1k","","","","Resistor_SMD:R_0603_1608Metric_Pad0.98x0.95mm_HandSolder",""
"R_TOUCH_OG1","1","1k","","","","Resistor_SMD:R_0603_1608Metric_Pad0.98x0.95mm_HandSolder",""
"S_BOOT1","1","SW_BOOT1","","","","CK_PTS526:CK_PTS526","https://www.ckswitches.com/products/switches/product-details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"
"S_RST1","1","SW_RST","","","","CK_PTS526:CK_PTS526","https://www.ckswitches.com/products/switches/product-details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"
"U1","1","LMR33630ADDA","","","","LMR33630ADDA:DDA0008J","https://www.ti.com/lit/gpn/lmr33630"
"U2","1","MAX98357AETE_T","","","","MAX98357AETE_T:QFN50P300X300X80-17N","https://www.analog.com/media/en/technical-documentation/data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"
